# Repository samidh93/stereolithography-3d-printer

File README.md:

# stereolithography 3d printer

## description

SLA 3d printer was created and developped during this project.
The main goal is to print a cylindre using a resonant laser system.
in this repo you will find:
- software stack written in c on stm32 microcontroller [main](/Src/main.c)
- pcb designed with eagle [pcb](pcb_eagle/)
- documentation and contributions [report](3D%20Drucker_Reser12_V5.pdf)

## Picture from inside the printer 

## picture from outside the printer

## demonstartion of running

[running mp4 ideo with sound](running.mp4)

## demonstartion of printing

[printing mp4 video with sound](printing.mp4)

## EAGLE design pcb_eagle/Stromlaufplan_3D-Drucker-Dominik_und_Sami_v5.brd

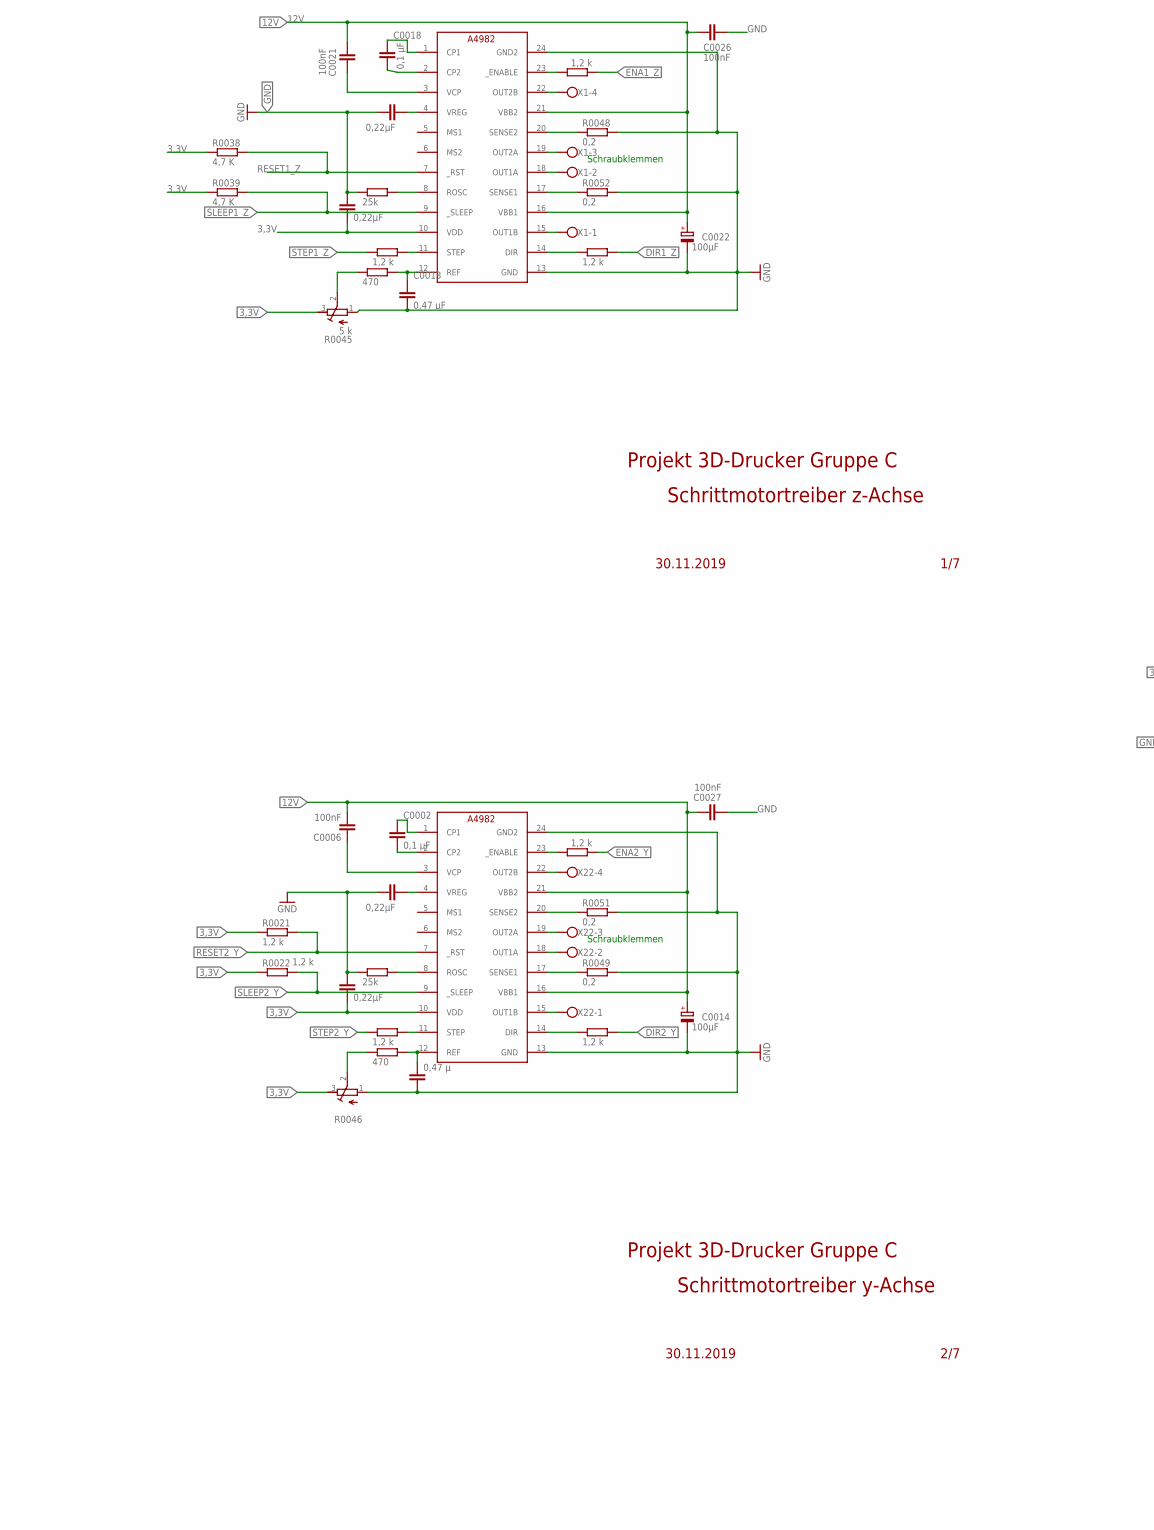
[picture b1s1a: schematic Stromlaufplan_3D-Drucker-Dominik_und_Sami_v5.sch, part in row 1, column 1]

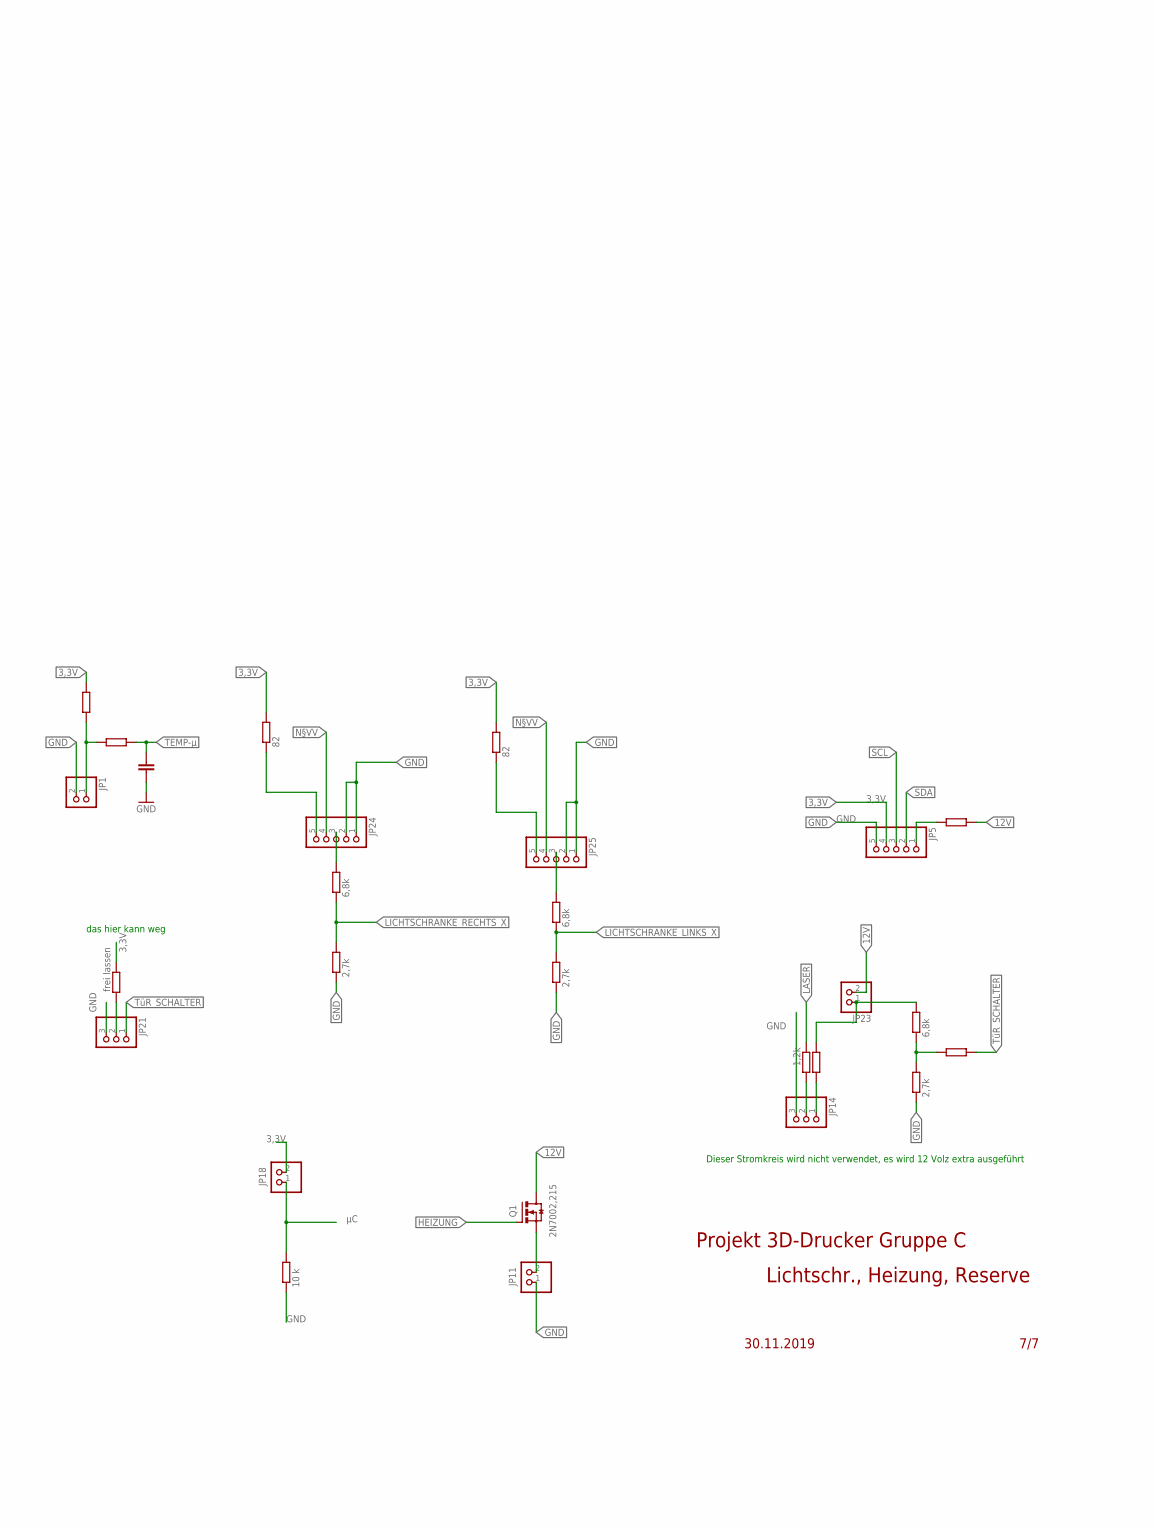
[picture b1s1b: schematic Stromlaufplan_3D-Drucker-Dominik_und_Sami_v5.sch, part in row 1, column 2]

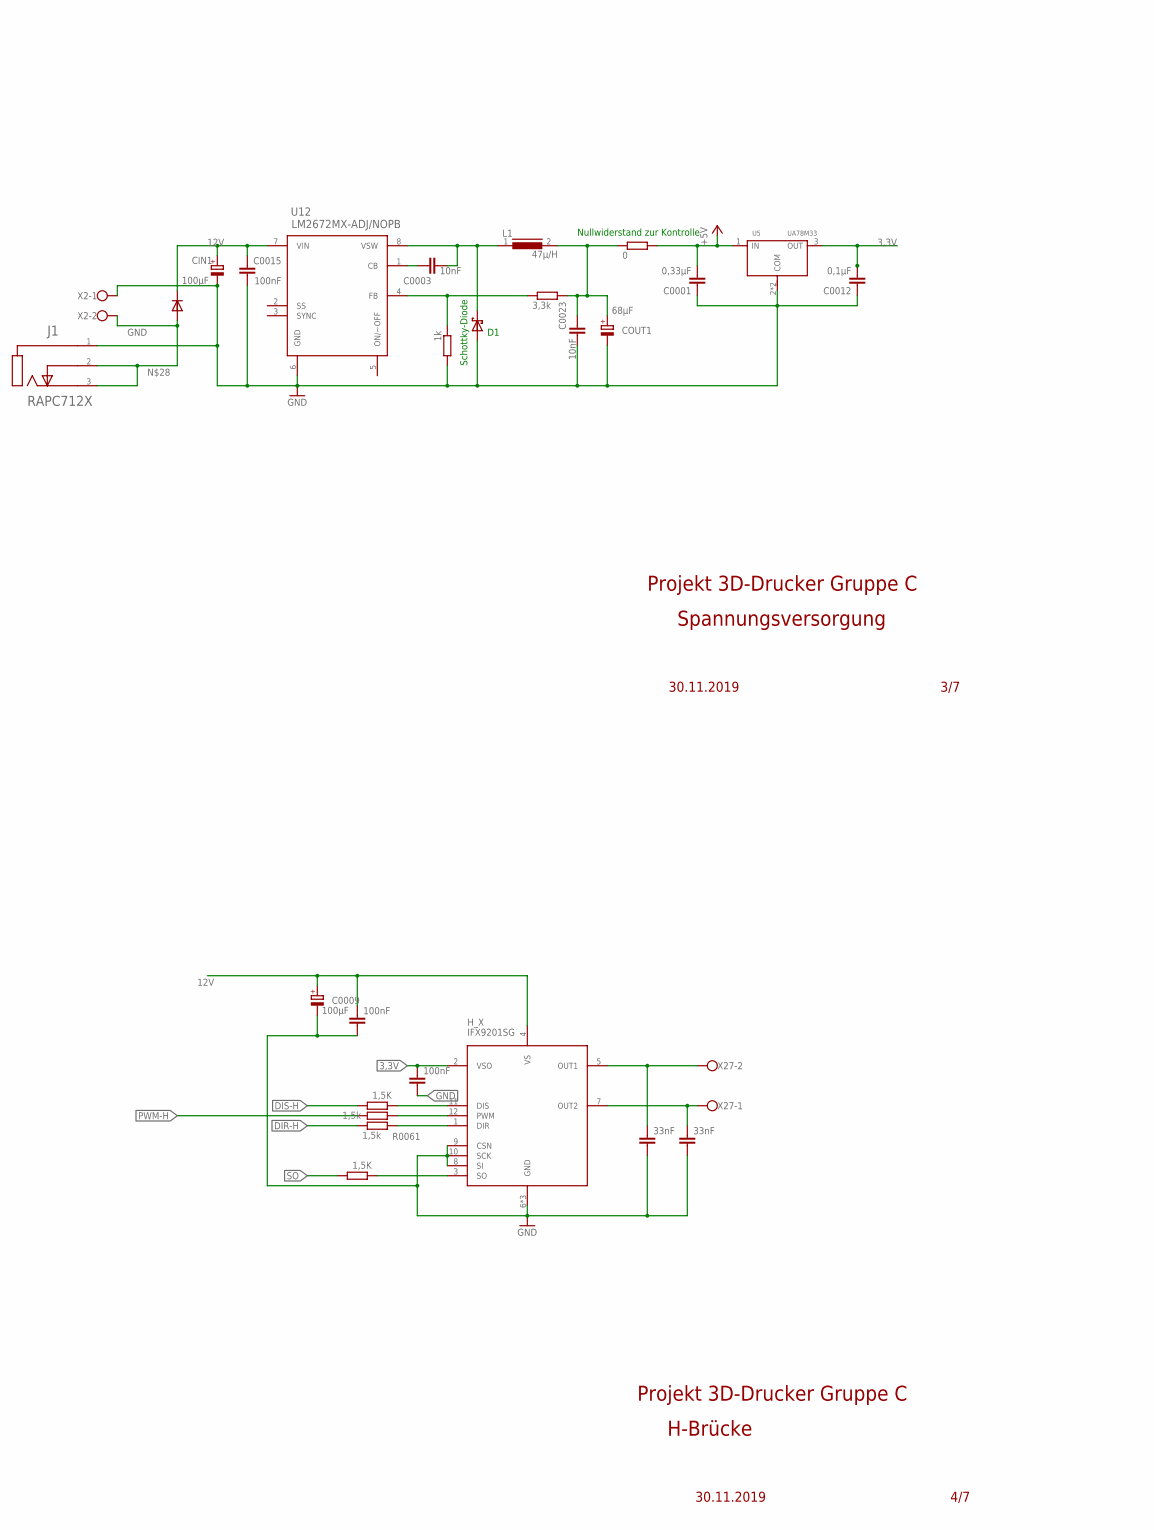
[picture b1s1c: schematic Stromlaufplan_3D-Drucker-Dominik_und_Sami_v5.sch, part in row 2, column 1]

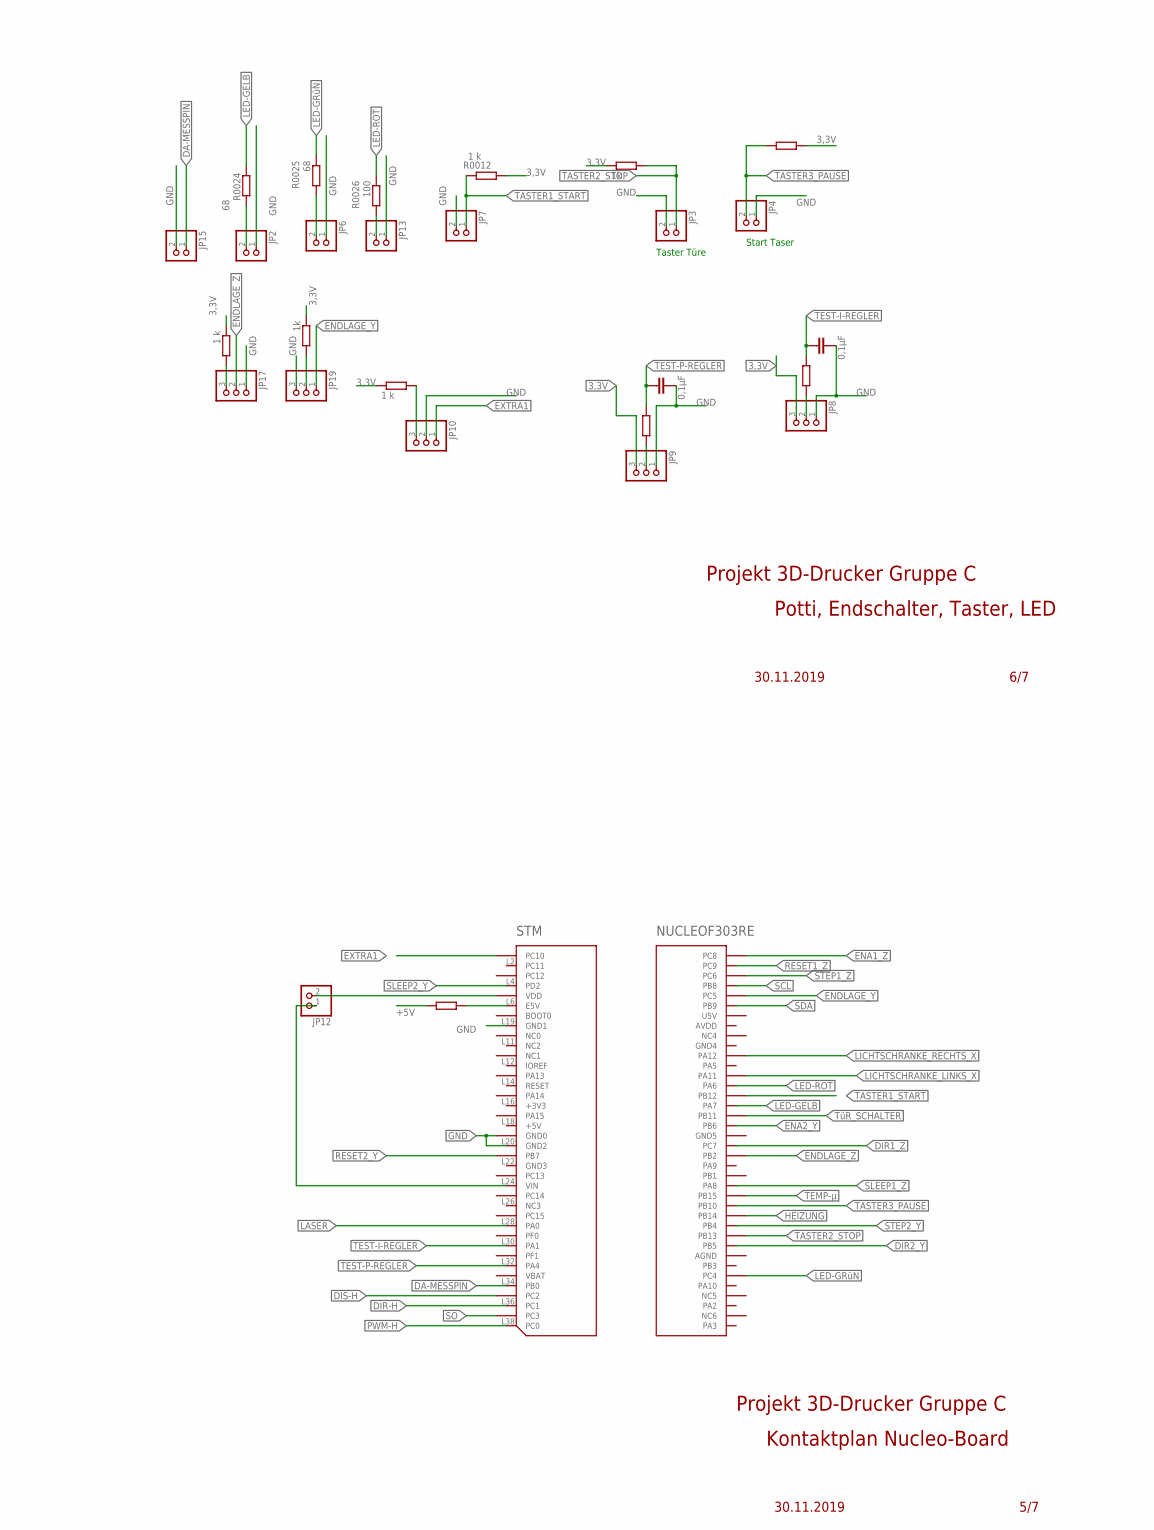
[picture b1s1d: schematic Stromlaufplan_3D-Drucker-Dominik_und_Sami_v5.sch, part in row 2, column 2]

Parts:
A4982_Y, A4982_Y1: A4982_STEPDRIVER; TSSOP24
C0001: 0,33µF; C0603
C0002, C0018: 0,1 µF; C0603
C0003, C0023: 10nF; C0603
C0004, C0005, C0019, C0020: 0,22µF; C0603
C0006, C0015, C0021, C0026, C0027: 100nF; C0603
C0007, C0008: 33nF; C0805
C0009, C0014, C0022: 100µF; UD-8X10_NICHICON
C0010: 0,47 µ; C0805
C0011: C-EUC0805; C0805
C0012, C0024, C0025: 0,1µF; C0603
C0013: 0,47 µF; C0603
C0016, C0041: 100nF; C0805
CIN1: 100µF; 140CLH-1010
COUT1: 68µF; 140CLH-1010
D1: 1N5819HW-7-F; SOD-123_MINI-SMA
D12: MURS360BT3G; SMB
H_X: IFX9201SG; BSOP-12
J1: RAPC712X; SWC_RAPC712X
JP1, JP2, JP3, JP4, JP6, JP7, JP11, JP12, JP13, JP15, JP18, JP23: PINHD-1X2; 1X02
JP5, JP24, JP25: PINHD-1X5; 1X05
JP8, JP9, JP10, JP14, JP17, JP19, JP21: PINHD-1X3; 1X03
L1: 47µ/H; INDUCTOR
Q1: 2N7002,215; SOT23-3
R0001, R0063: 1,5K; R0603
R0002, R0005, R0043: 6,8k; R0603
R0003, R0013: 1k; R0603
R0004, R0028, R0044: 2,7k; R0603
R0006, R0019: 25k; R0603
R0007: 10 k; R0603
R0008, R0014, R0016, R0017, R0020, R0027, R0030, R0031, R0053: R-EU_R0603; R0603
R0009, R0010, R0011, R0021, R0022, R0034, R0035, R0036: 1,2 k; R0603
R0012, R0015, R0033: 1 k; R0603
R0018: frei lassen; R0603
R0023, R0037: 470; R0603
R0024, R0025: 68; R0603
R0026: 100; R0603
R0029, R0032: 82; R0603
R0038, R0039: 4,7 K; R0603
R0042: 1,2k; R0603
R0045: 5 k; RTRIM3296Y
R0046: R-TRIMM3296Y; RTRIM3296Y
R0048, R0049, R0051, R0052: 0,2; R2512
R0061, R0062: 1,5k; R0603
STM: NUCLEOF303RE; DIL40
TEST_R: 0; R0603
TEST_R2: 3,3k; R0603
TEST_R3: 1k; R0603
U5: UA78M33; SOT-223
U12: LM2672MX-ADJ/NOPB; SOIC-8
X1, X22: SCHRAUBKLEMME_4X; W237-4
X2, X27: SCHRAUBKLEMME_2X; W237-102

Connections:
3,3V: A4982_Y.10 (VDD), A4982_Y1.10 (VDD), C0005.1, C0012.2, C0016.1, C0020.1, H_X.2 (VSO), JP5.4, JP8.3, JP9.3, JP18.2, R0003.1, R0008.1, R0012.1, R0013.1, R0014.1, R0015.1, R0018.1, R0021.1, R0022.1, R0029.2, R0032.2, R0033.1, R0038.1, R0039.1, R0045.3 (E), R0046.3 (E), U5.3 (OUT)
12V: A4982_Y.16 (VBB1), A4982_Y.21 (VBB2), A4982_Y1.16 (VBB1), A4982_Y1.21 (VBB2), C0006.2, C0009.+, C0014.+, C0015.2, C0021.2, C0022.+, C0026.2, C0027.1, C0041.1, CIN1.+, D12.1, H_X.4 (VS), JP14.1, JP23.2, Q1.3 (D), R0016.2, R0030.2, U12.7 (VIN)
+5V: C0001.2, R0027.1, TEST_R.2, U5.1 (IN)
DA-MESSPIN: JP15.1, STM.L34 (PB0)
DIR1_Z: R0036.2, STM.R19 (PC7)
DIR2_Y: R0011.2, STM.R29 (PB5)
DIR-H: R0061.1, STM.L36 (PC1)
DIS-H: R0063.1, STM.L35 (PC2)
ENA1_Z: R0034.1, STM.R2 (PC8)
ENA2_Y: R0009.1, STM.R17 (PB6)
ENDLAGE_Y: JP19.1, STM.R6 (PC5)
ENDLAGE_Z: JP17.2, STM.R22 (PB2)
EXTRA1: JP10.1, STM.L1 (PC10)
GND: A4982_Y.13 (GND), A4982_Y.24 (GND2), A4982_Y1.13 (GND), A4982_Y1.24 (GND2), C0001.1, C0004.2, C0005.2, C0007.2, C0008.2, C0009.-, C0010.2, C0011.2, C0012.1, C0013.2, C0014.-, C0015.1, C0016.2, C0019.2, C0020.2, C0022.-, C0023.2, C0024.1, C0025.1, C0026.1, C0027.2, C0041.2, CIN1.-, COUT1.-, D1.A, H_X.6 (GND), H_X.8 (SI), H_X.9 (CSN), H_X.10 (SCK), H_X.PAD (GND), H_X.PAD2 (GND), J1.1 (CENTER_PIN), JP1.2, JP2.1, JP3.2, JP4.1, JP5.5, JP6.1, JP7.2, JP8.1, JP9.1, JP10.2, JP11.1, JP13.1, JP14.3, JP15.2, JP17.1, JP19.3, JP21.3, JP24.1, JP24.2, JP25.1, JP25.2, R0004.1, R0006.1, R0007.1, R0019.1, R0028.1, R0044.1, R0045.1 (A), R0046.1 (A), R0048.2, R0049.2, R0051.2, R0052.2, STM.L8 (GND0), STM.L19 (GND1), STM.L20 (GND2), TEST_R3.2, U5.2 (COM), U5.TER (COM), U12.6 (GND), X2.1
HEIZUNG: Q1.1 (G), STM.R28 (PB14)
LASER: R0042.1, STM.L28 (PA0)
LED-GELB: R0024.2, STM.R15 (PA7)
LED-GRüN: R0025.1, STM.R34 (PC4)
LED-ROT: R0026.1, STM.R13 (PA6)
LICHTSCHRANKE_LINKS_X: R0005.1, R0028.2, STM.R14 (PA11)
LICHTSCHRANKE_RECHTS_X: R0002.1, R0004.2, STM.R12 (PA12)
unnamed: A4982_Y1.2 (CP2), C0018.2
unnamed: JP17.3, R0015.2
unnamed: JP24.5, R0029.1
unnamed: R0023.1, R0046.2 (S)
unnamed: C0003.1, U12.1 (CB)
unnamed: JP2.2, R0024.1
unnamed: A4982_Y.12 (REF), C0010.1, R0023.2
unnamed: A4982_Y.2 (CP2), C0002.2
unnamed: A4982_Y.1 (CP1), C0002.1
unnamed: A4982_Y.3 (VCP), C0006.1
unnamed: JP19.2, R0003.2
unnamed: A4982_Y.4 (VREG), C0004.1
unnamed: A4982_Y1.12 (REF), C0013.1, R0037.2
unnamed: A4982_Y1.1 (CP1), C0018.1
unnamed: A4982_Y.18 (OUT1A), X22.2
unnamed: A4982_Y.15 (OUT1B), X22.1
unnamed: A4982_Y.19 (OUT2A), X22.3
unnamed: A4982_Y.22 (OUT2B), X22.4
unnamed: A4982_Y.17 (SENSE1), R0049.1
unnamed: A4982_Y.20 (SENSE2), R0051.1
unnamed: A4982_Y.8 (ROSC), R0006.2
unnamed: A4982_Y.23 (_ENABLE), R0009.2
unnamed: H_X.3 (SO), R0001.2
unnamed: A4982_Y.14 (DIR), R0011.1
unnamed: A4982_Y1.4 (VREG), C0019.1
unnamed: A4982_Y1.15 (OUT1B), X1.1
unnamed: JP23.1, R0016.1, R0043.2
unnamed: D12.2, J1.2 (SHUNT), J1.3 (SLEEVE), X2.2
unnamed: C0023.1, COUT1.+, L1.2, TEST_R.1, TEST_R2.2
unnamed: A4982_Y1.19 (OUT2A), X1.3
unnamed: C0003.2, D1.C, L1.1, U12.8 (VSW)
unnamed: JP9.2, R0031.1
unnamed: JP24.3, R0002.2
unnamed: JP25.3, R0005.2
unnamed: R0017.1, R0043.1, R0044.2
unnamed: JP8.2, R0053.1
unnamed: A4982_Y1.22 (OUT2B), X1.4
unnamed: JP11.2, Q1.2 (S)
unnamed: A4982_Y1.17 (SENSE1), R0052.1
unnamed: JP6.2, R0025.2
unnamed: JP13.2, R0026.2
unnamed: A4982_Y1.20 (SENSE2), R0048.1
unnamed: A4982_Y1.8 (ROSC), R0019.2
unnamed: A4982_Y1.23 (_ENABLE), R0034.2
unnamed: H_X.1 (DIR), R0061.2
unnamed: H_X.12 (PWM), R0062.2
unnamed: C0007.1, H_X.5 (OUT1), X27.2
unnamed: JP5.1, R0030.1
unnamed: A4982_Y1.14 (DIR), R0036.1
unnamed: JP25.5, R0032.1
unnamed: JP10.3, R0033.2
unnamed: JP14.2, R0042.2
unnamed: JP1.1, R0008.2, R0020.2
unnamed: A4982_Y1.18 (OUT1A), X1.2
unnamed: A4982_Y1.3 (VCP), C0021.1
unnamed: JP12.2, STM.L5 (VDD)
unnamed: R0037.1, R0045.2 (S)
unnamed: JP12.1, STM.L24 (VIN)
unnamed: R0027.2, STM.L6 (E5V)
unnamed: JP21.2, R0018.2
unnamed: H_X.11 (DIS), R0063.2
unnamed: C0008.1, H_X.7 (OUT2), X27.1
N§VV: JP24.4, JP25.4, TEST_R2.1, TEST_R3.1, U12.4 (FB)
PWM-H: R0062.1, STM.L38 (PC0)
RESET1_Z: A4982_Y1.7 (_RST), R0038.2, STM.R1 (PC9)
RESET2_Y: A4982_Y.7 (_RST), R0021.2, STM.L21 (PB7)
SCL: JP5.3, STM.R3 (PB8)
SDA: JP5.2, STM.R5 (PB9)
SLEEP1_Z: A4982_Y1.9 (_SLEEP), R0039.2, STM.R23 (PA8)
SLEEP2_Y: A4982_Y.9 (_SLEEP), R0022.2, STM.L4 (PD2)
SO: R0001.1, STM.L37 (PC3)
STEP1_Z: R0035.1, STM.R4 (PC6)
STEP2_Y: R0010.1, STM.R27 (PB4)
STP1: A4982_Y.11 (STEP), R0010.2
STP2: A4982_Y1.11 (STEP), R0035.2
TASTER1_START: JP7.1, R0012.2, STM.R16 (PB12)
TASTER2_STOP: JP3.1, R0013.2, STM.R30 (PB13)
TASTER3_PAUSE: JP4.2, R0014.2, STM.R25 (PB10)
TEMP-µ: C0011.1, R0020.1, STM.R26 (PB15)
TEST-I-REGLER: C0025.2, R0053.2, STM.L30 (PA1)
TEST-P-REGLER: C0024.2, R0031.2, STM.L32 (PA4)
TüR_SCHALTER: JP21.1, R0017.2, STM.R18 (PB11)
µC: JP18.1, R0007.2

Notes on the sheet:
Nullwiderstand zur Kontrolle
Schraubklemmen
das hier kann weg
Schottky-Diode
Dieser Stromkreis wird nicht verwendet, es wird 12 Volz extra ausgeführt
Start Taser
Taster Türe
Schrittmotortreiber z-Achse
1/7
Schrittmotortreiber y-Achse
Spannungsversorgung
H-Brücke
Kontaktplan Nucleo-Board
Potti, Endschalter, Taster, LED
Lichtschr., Heizung, Reserve
2/7
3/7
5/7
6/7
7/7
4/7
Projekt 3D-Drucker Gruppe C
30.11.2019

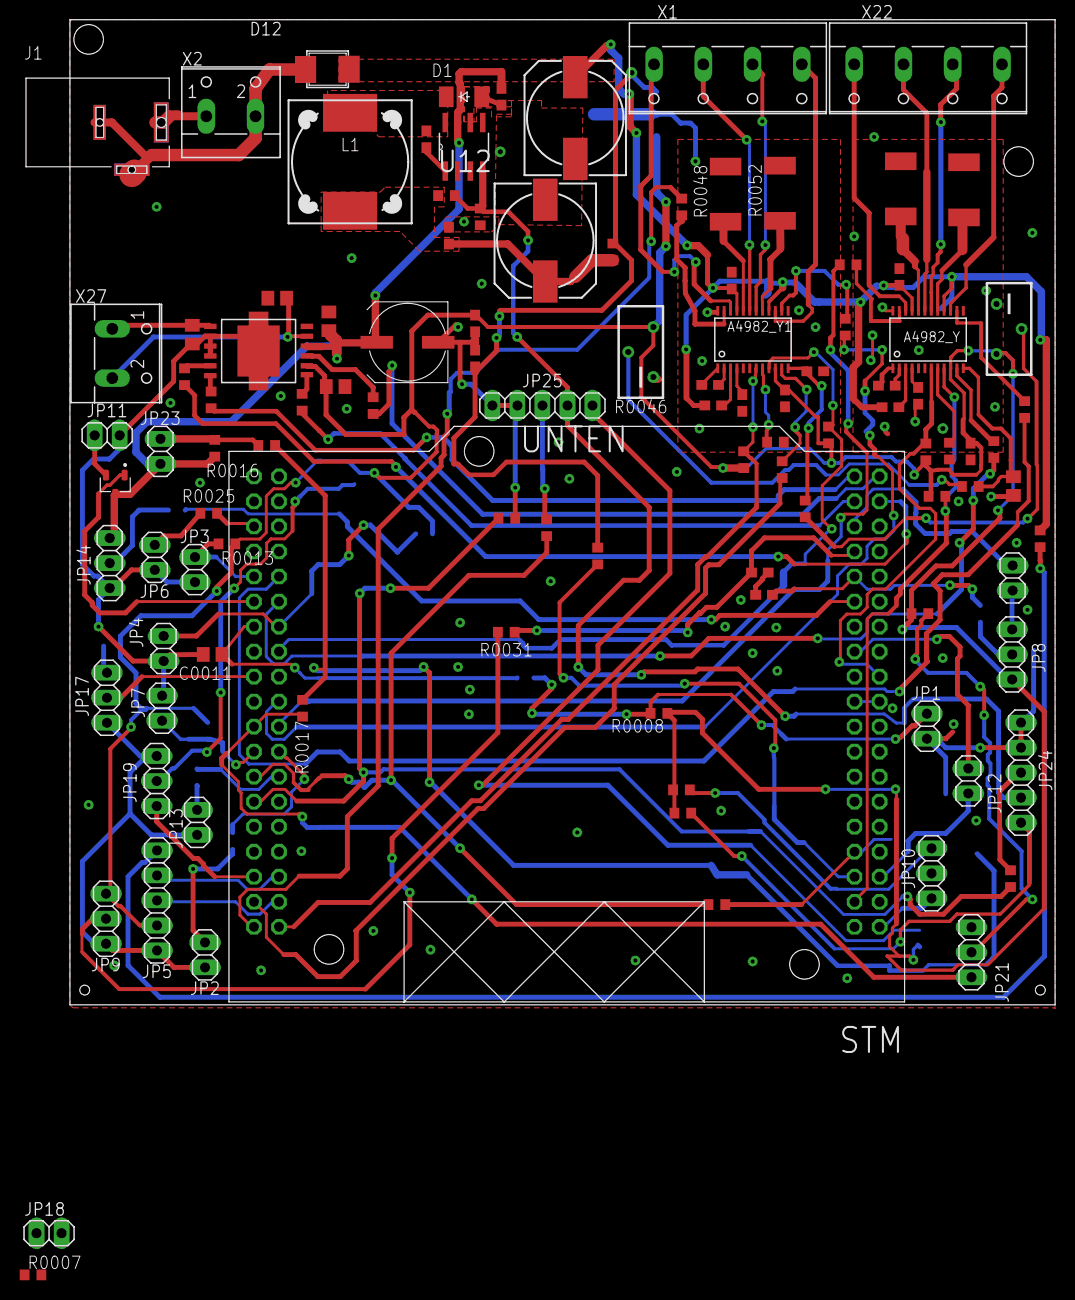
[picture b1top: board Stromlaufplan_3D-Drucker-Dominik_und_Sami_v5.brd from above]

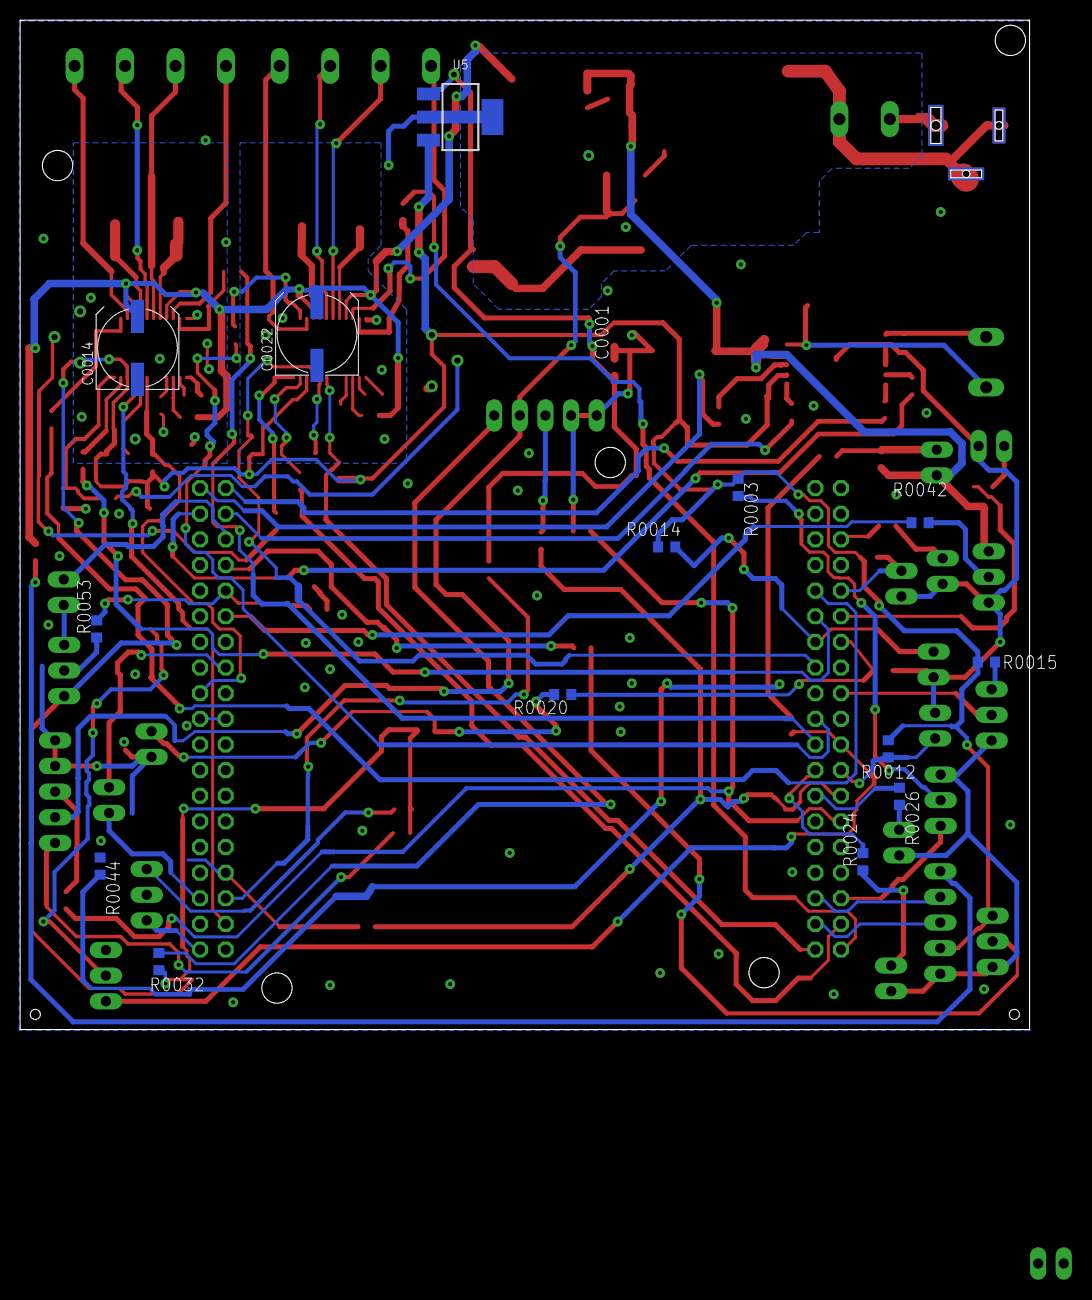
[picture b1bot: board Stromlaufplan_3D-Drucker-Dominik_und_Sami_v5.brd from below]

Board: 2 copper layers, 100.0 x 100.0 mm, 121 parts (14 on the bottom side), 104 nets.

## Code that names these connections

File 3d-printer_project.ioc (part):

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Mcu.Name=STM32F303R(D-E)Tx
Mcu.Package=LQFP64
Mcu.UserName=STM32F303RETx
PA0.GPIOParameters=GPIO_Label
PA0.GPIO_Label=Laser
PA0.Signal=GPIO_Output
PA1.GPIOParameters=GPIO_Label
PA1.GPIO_Label=TEST-I-Regler 
PA1.Mode=IN2-Single-Ended
PA1.Signal=ADC1_IN2
PA11.GPIOParameters=GPIO_Label
PA11.GPIO_Label=LICHTSCHRANKE
PA11.Signal=S_TIM4_CH1
PA13.GPIOParameters=GPIO_Label
PA13.GPIO_Label=TMS
PA13.Mode=Serial_Wire
PA13.Signal=SYS_JTMS-SWDIO
PA14.GPIOParameters=GPIO_Label
PA14.GPIO_Label=TCK
PA14.Mode=Serial_Wire
PA14.Signal=SYS_JTCK-SWCLK
PA2.GPIOParameters=GPIO_Speed,GPIO_PuPd,GPIO_Label,GPIO_Mode
PA2.GPIO_Label=USART_TX
PA2.GPIO_Mode=GPIO_MODE_AF_PP
PA2.GPIO_PuPd=GPIO_NOPULL
PA2.GPIO_Speed=GPIO_SPEED_FREQ_LOW
PA2.Mode=Asynchronous
PA2.Signal=USART2_TX
PA3.GPIOParameters=GPIO_Speed,GPIO_PuPd,GPIO_Label,GPIO_Mode
PA3.GPIO_Label=USART_RX
PA3.GPIO_Mode=GPIO_MODE_AF_PP
PA3.GPIO_PuPd=GPIO_NOPULL
PA3.GPIO_Speed=GPIO_SPEED_FREQ_LOW
PA3.Mode=Asynchronous
PA3.Signal=USART2_RX
PA4.GPIOParameters=GPIO_Label
PA4.GPIO_Label=TEST-P-REGLER 
PA4.Mode=IN1-Single-Ended
PA4.Signal=ADC2_IN1
PA5.GPIOParameters=GPIO_Speed,GPIO_PuPd,GPIO_Label,GPIO_Mode
PA5.GPIO_Label=LD2 [Green Led]
PA5.GPIO_Mode=GPIO_MODE_OUTPUT_PP
PA5.GPIO_PuPd=GPIO_NOPULL
PA5.GPIO_Speed=GPIO_SPEED_FREQ_LOW
PA5.Signal=GPIO_Output
PA6.GPIOParameters=GPIO_Label
PA6.GPIO_Label=LED-ROT 
PA6.Signal=GPIO_Output
PA7.GPIOParameters=GPIO_Label
PA7.GPIO_Label=LED-GELB 
PA7.Signal=GPIO_Output
PA8.GPIOParameters=GPIO_Label
PA8.GPIO_Label=SLEEP1_Z 
PA8.Signal=GPIO_Output
PB0.GPIOParameters=GPIO_Label
PB0.GPIO_Label=DAC-MESSPIN 
PB0.Signal=GPIO_Analog
PB1.Mode=IN1-Single-Ended
PB1.Signal=ADC3_IN1
PB10.GPIOParameters=GPIO_PuPd,GPIO_Label
PB10.GPIO_Label=TASTER3_PAUSE 
PB10.GPIO_PuPd=GPIO_PULLDOWN
PB10.Signal=GPXTI10
PB11.GPIOParameters=GPIO_PuPd,GPIO_Label
PB11.GPIO_Label=T\u00DCR_SCHALTER 
PB11.GPIO_PuPd=GPIO_PULLDOWN
PB11.Signal=GPXTI11
PB12.GPIOParameters=GPIO_PuPd,GPIO_Label
PB12.GPIO_Label=TASTER1_START 
PB12.GPIO_PuPd=GPIO_PULLDOWN
PB12.Signal=GPXTI12
PB14.GPIOParameters=GPIO_Label
PB14.GPIO_Label=HEIZUNG-PWM
PB14.Signal=S_TIM15_CH1
PB15.GPIOParameters=GPIO_Label
PB15.GPIO_Label=TEMP-Mess
PB15.Mode=IN5-Single-Ended
PB15.Signal=ADC4_IN5
PB2.GPIOParameters=GPIO_PuPd,GPIO_Label
PB2.GPIO_Label=ENDLAGE_Z 
PB2.GPIO_PuPd=GPIO_PULLDOWN
PB2.Signal=GPIO_Input
PB3.GPIOParameters=GPIO_Label
PB3.GPIO_Label=SWO
PB3.Signal=SYS_JTDO-TRACESWO
PB4.GPIOParameters=GPIO_Label
PB4.GPIO_Label=STEP2_Y
PB4.Signal=GPIO_Output
PB5.GPIOParameters=GPIO_Label
PB5.GPIO_Label=DIR2_Y 
PB5.Signal=GPIO_Output
PB6.GPIOParameters=GPIO_FM6,GPIO_PuPd,GPIO_Label
PB6.GPIO_FM6=__NULL
PB6.GPIO_Label=ENA2_Y 
PB6.GPIO_PuPd=GPIO_NOPULL
PB6.Signal=GPIO_Output
PB7.GPIOParameters=PinState,GPIO_PuPd,GPIO_Label
PB7.GPIO_Label=RESET2_Y 
PB7.GPIO_PuPd=GPIO_NOPULL
PB7.PinState=GPIO_PIN_RESET
PB7.Signal=GPIO_Output
PB8.GPIOParameters=GPIO_Label
PB8.GPIO_Label=SCL  
PB8.Mode=I2C
PB8.Signal=I2C1_SCL
PB9.GPIOParameters=GPIO_Label
PB9.GPIO_Label=SDA 
PB9.Mode=I2C
PB9.Signal=I2C1_SDA
PC0.GPIOParameters=GPIO_Label
PC0.GPIO_Label=PWM-H 
PC0.Signal=S_TIM1_CH1
PC1.GPIOParameters=GPIO_Label
PC1.GPIO_Label=DIR-H 
PC1.Signal=GPIO_Output
PC10.GPIOParameters=GPIO_Label
PC10.GPIO_Label=Extra
PC10.Signal=GPIO_Output
PC13.GPIOParameters=GPIO_PuPd,GPIO_Label,GPIO_ModeDefaultEXTI
PC13.GPIO_Label=Blue_pushbutton
PC13.GPIO_ModeDefaultEXTI=GPIO_MODE_IT_RISING_FALLING
PC13.GPIO_PuPd=GPIO_PULLDOWN
PC13.Signal=GPXTI13
PC14-OSC32_IN.Signal=RCC_OSC32_IN
PC15-OSC32_OUT.Signal=RCC_OSC32_OUT
PC2.GPIOParameters=GPIO_Label
PC2.GPIO_Label=DIS-H 
PC2.Signal=GPIO_Output
PC3.GPIOParameters=GPIO_Label
PC3.GPIO_Label=SO-H 
PC3.Signal=GPIO_Output
PC4.GPIOParameters=GPIO_Label
PC4.GPIO_Label=LED-GR\u00DCN 
PC4.Signal=GPIO_Output
PC5.GPIOParameters=GPIO_PuPd,GPIO_Label
PC5.GPIO_Label=ENDLAGE_Y 
PC5.GPIO_PuPd=GPIO_PULLDOWN
PC5.Signal=GPIO_Input
PC6.GPIOParameters=GPIO_Label
PC6.GPIO_Label=STEP1_Z
PC6.Signal=GPIO_Output
PC7.GPIOParameters=GPIO_Label
PC7.GPIO_Label=DIR1_Z 
PC7.Signal=GPIO_Output
PC8.GPIOParameters=GPIO_Label
PC8.GPIO_Label=ENA1_Z 
PC8.Signal=GPIO_Output
PC9.GPIOParameters=GPIO_Label
PC9.GPIO_Label=RESET1_Z 
PC9.Signal=GPIO_Output
PD2.GPIOParameters=PinState,GPIO_PuPd,GPIO_Label
PD2.GPIO_Label=SLEEP2_Y 
PD2.GPIO_PuPd=GPIO_NOPULL
PD2.PinState=GPIO_PIN_RESET
PD2.Signal=GPIO_Output
PF0-OSC_IN.Signal=RCC_OSC_IN
PF1-OSC_OUT.Signal=RCC_OSC_OUT
RCC.HSE_VALUE=8000000
RCC.SYSCLKFreq_VALUE=72000000
RCC.SYSCLKSourceVirtual=RCC_SYSCLKSOURCE_PLLCLK
board=NUCLEO-F303RE
boardIOC=true

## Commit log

2021-03-23 added files
2021-03-23 added pcb
2021-03-23 added readme
2021-03-23 added documentation
